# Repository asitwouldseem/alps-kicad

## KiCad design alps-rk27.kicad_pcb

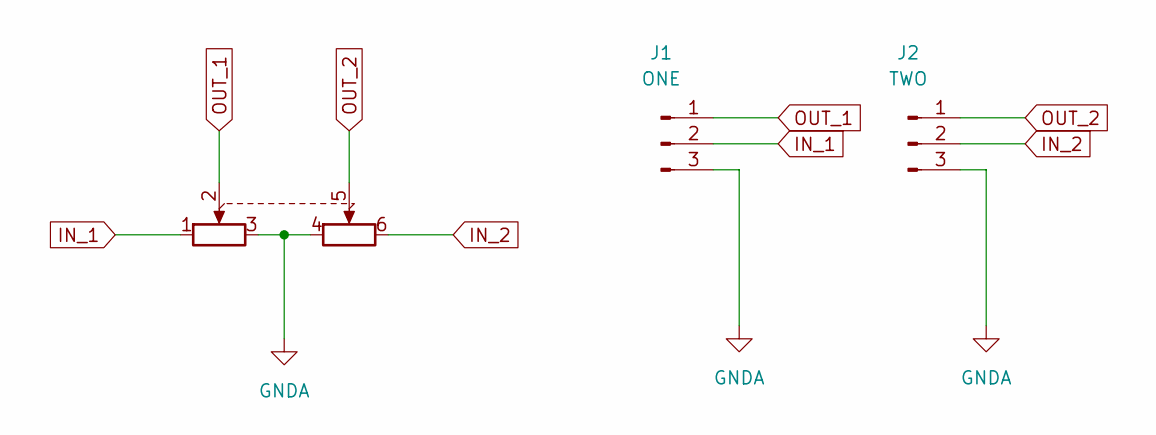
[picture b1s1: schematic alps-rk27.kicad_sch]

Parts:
J1: ONE; JST_XH_B3B-XH-A_1x03_P2.50mm_Vertical
J2: TWO; JST_XH_B3B-XH-A_1x03_P2.50mm_Vertical
RV1: R_Potentiometer_Dual; Alps_RK27

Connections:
GNDA: J1.3, J2.3, RV1.3, RV1.4
IN_1: J1.2, RV1.1
IN_2: J2.2, RV1.6
OUT_1: J1.1, RV1.2
OUT_2: J2.1, RV1.5

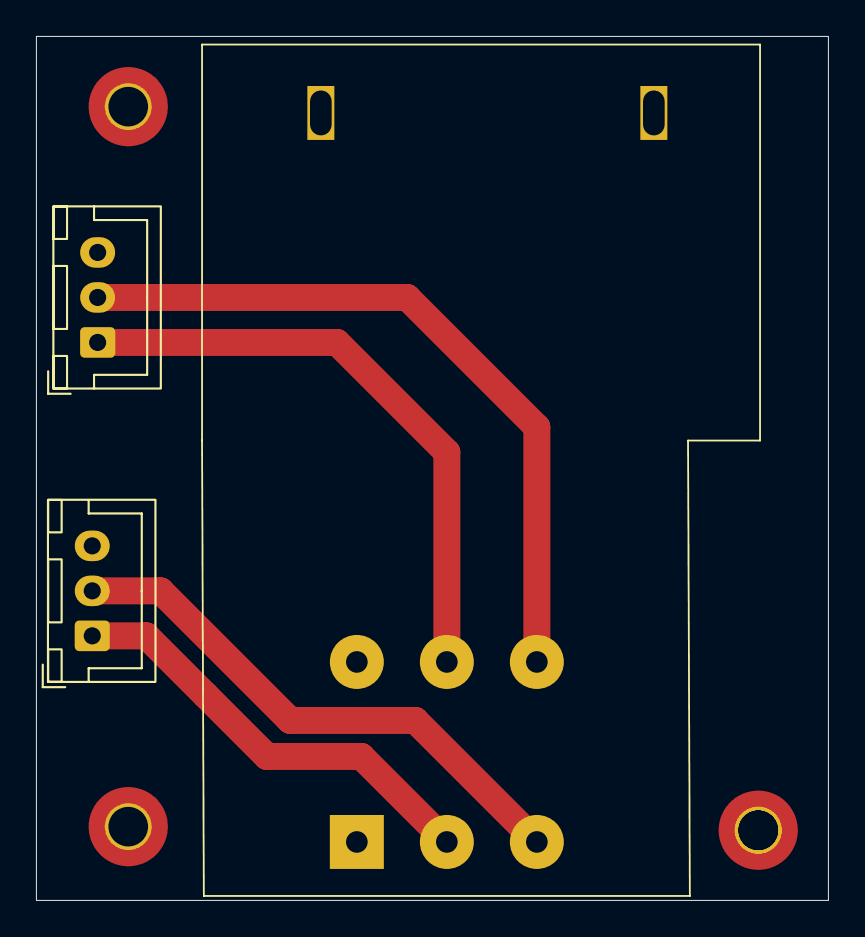
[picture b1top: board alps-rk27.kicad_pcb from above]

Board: 2 copper layers, 44.0 x 48.0 mm, 3 parts (0 on the bottom side), 5 nets.

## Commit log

2026-05-10 Make the fill the full board.
2026-06-07 Create gerbers
2026-06-21 Prepare for fab
